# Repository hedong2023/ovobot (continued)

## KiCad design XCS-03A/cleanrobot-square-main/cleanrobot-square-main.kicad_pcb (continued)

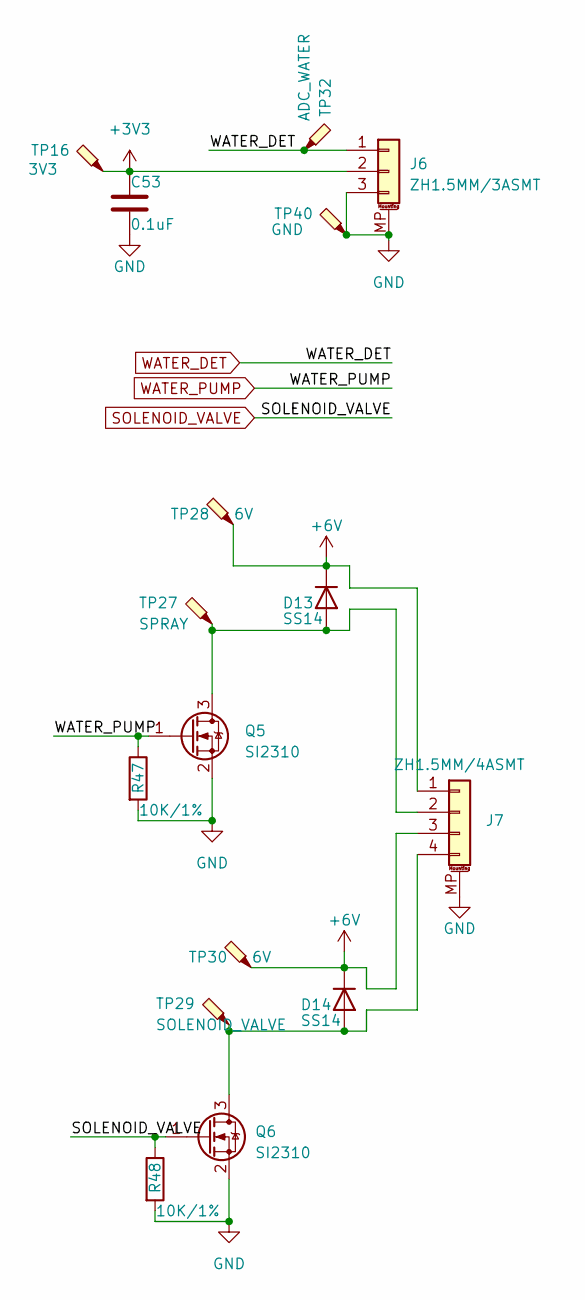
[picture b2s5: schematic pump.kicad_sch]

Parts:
C53: 0.1uF; C_0603_1608Metric
D13, D14: SS14; D_SOD-123
J6: ZH1.5MM/3ASMT; JST_ZH_B3B-ZR-SM4-TF_1x03-1MP_P1.50mm_Vertical
J7: ZH1.5MM/4ASMT; JST_ZH_B4B-ZR-SM4-TF_1x04-1MP_P1.50mm_Vertical
Q5, Q6: SI2310; SOT-23
R47, R48: 10K/1%; R_0603_1608Metric
TP16: 3V3; TestPoint_Pad_D1.0mm
TP27: SPRAY; TestPoint_Pad_D1.0mm
TP28, TP30: 6V; TestPoint_Pad_D1.0mm
TP29: SOLENOID_VALVE; TestPoint_Pad_D1.0mm
TP32: ADC_WATER; TestPoint_Pad_D1.0mm
TP40: GND; TestPoint_Pad_D1.0mm

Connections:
+3V3: C53.1, J6.2, TP16.1; also elsewhere on the board
+6V: D13.1 (K), D14.1 (K), J7.1, J7.3, TP28.1, TP30.1; also elsewhere on the board
GND: C53.2, J6.3, J6.MP (MountPin), J7.MP (MountPin), Q5.2 (S), Q6.2 (S), R47.2, R48.2, TP40.1; also elsewhere on the board
unnamed: D13.2 (A), J7.2, Q5.3 (D), TP27.1
unnamed: D14.2 (A), J7.4, Q6.3 (D), TP29.1
SOLENOID_VALVE: Q6.1 (G), R48.1; also elsewhere on the board
WATER_DET: J6.1, TP32.1; also elsewhere on the board
WATER_PUMP: Q5.1 (G), R47.1; also elsewhere on the board

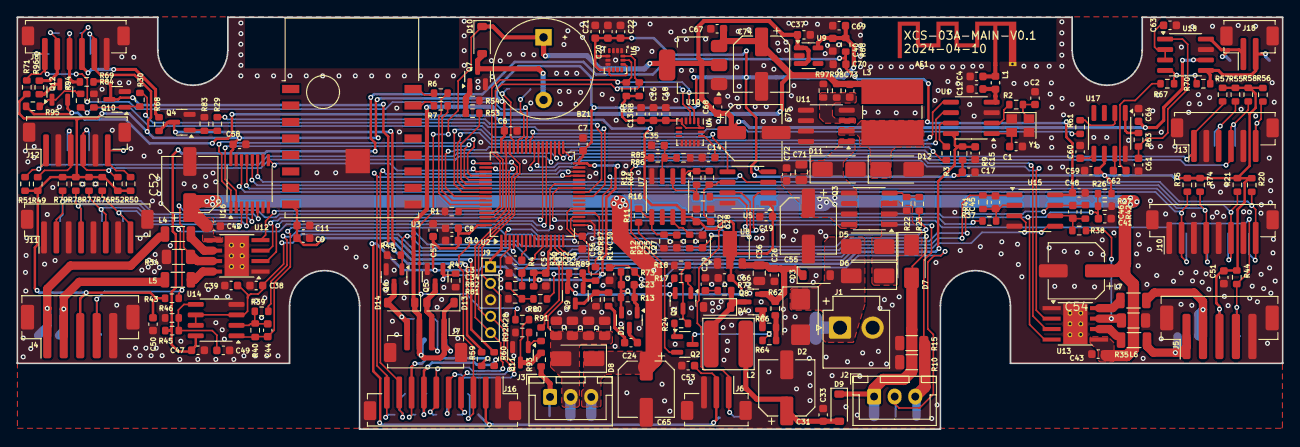
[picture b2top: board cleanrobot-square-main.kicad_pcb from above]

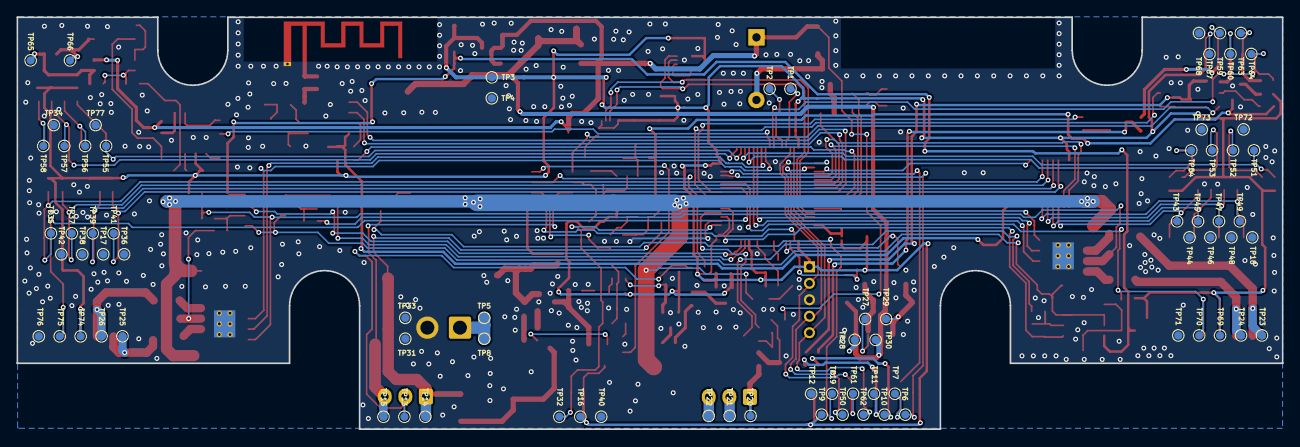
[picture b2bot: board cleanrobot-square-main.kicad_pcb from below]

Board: 2 copper layers, 153.6 x 50.0 mm, 319 parts (77 on the bottom side), 152 nets.

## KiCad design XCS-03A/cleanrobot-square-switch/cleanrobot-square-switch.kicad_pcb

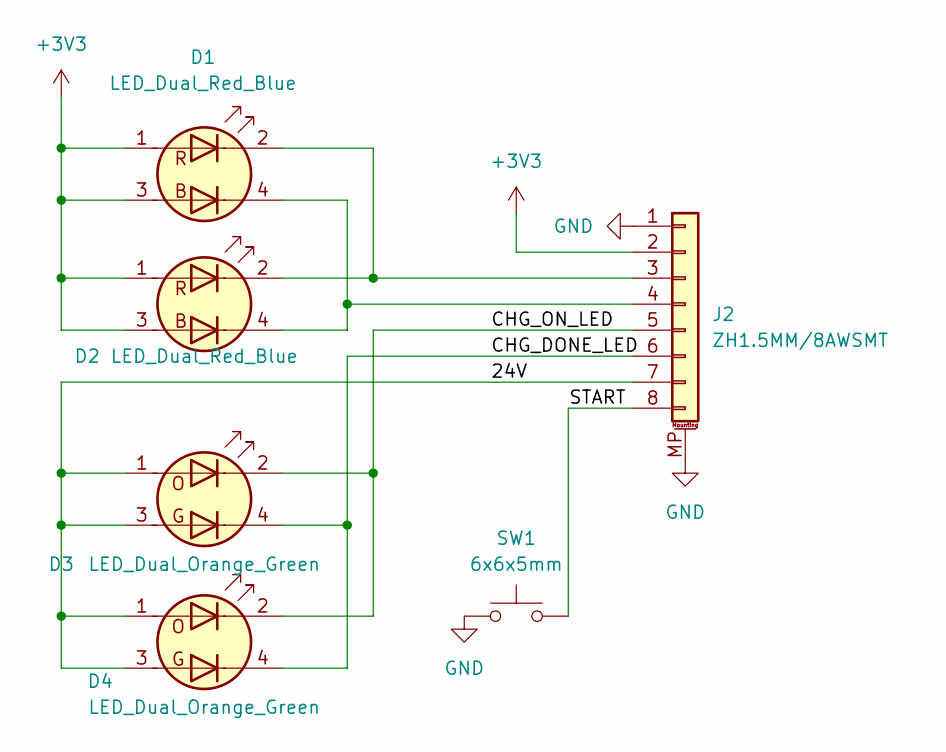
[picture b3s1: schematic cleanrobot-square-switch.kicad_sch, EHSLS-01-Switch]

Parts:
D1, D2: LED_Dual_Red_Blue; LED_Dual_1.6x1.5mm
D3, D4: LED_Dual_Orange_Green; LED_Dual_1.6x1.5mm
J2: ZH1.5MM/8AWSMT; JST_ZH_S8B-ZR-SM4-TF_1x08-1MP_P1.50mm_Horizontal
SW1: 6x6x5mm; SW_Push_1P1T_NO_6x6mm_H9.5mm

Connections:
+3V3: D1.1 (A1), D1.3 (A2), D2.1 (A1), D2.3 (A2), J2.2
/24V: D3.1 (A1), D3.3 (A2), D4.1 (A1), D4.3 (A2), J2.7
/CHG_DONE_LED: D3.4 (K2), D4.4 (K2), J2.6
/CHG_ON_LED: D3.2 (K1), D4.2 (K1), J2.5
/START: J2.8, SW1.2
GND: J2.1, J2.MP (MountPin), SW1.1
unnamed: D1.2 (K1), D2.2 (K1), J2.3
unnamed: D1.4 (K2), D2.4 (K2), J2.4

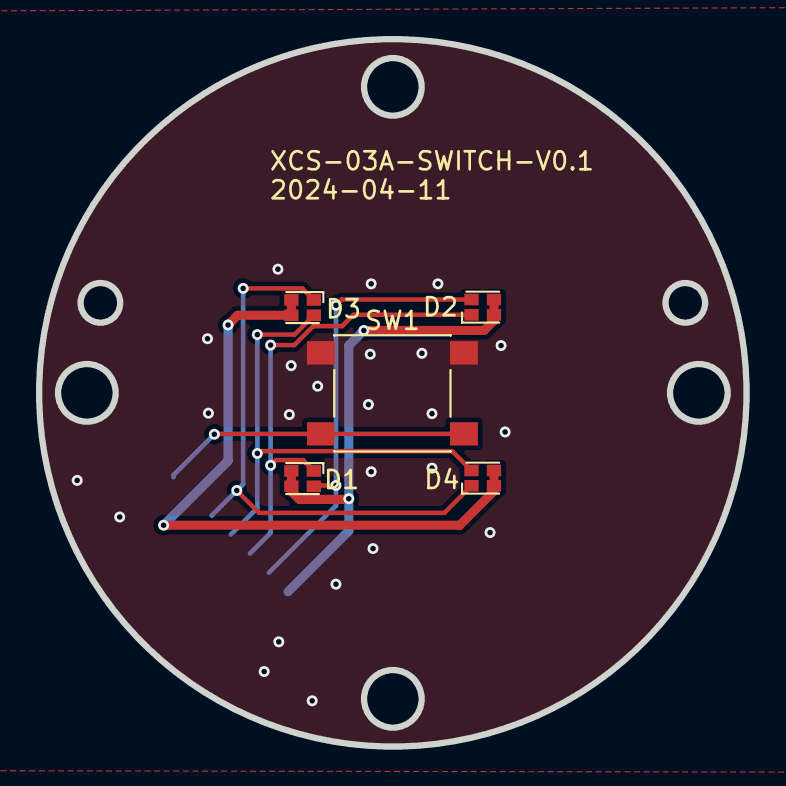
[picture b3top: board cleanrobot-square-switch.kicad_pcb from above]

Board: 2 copper layers, 39.3 x 39.3 mm, 6 parts (1 on the bottom side), 8 nets.
